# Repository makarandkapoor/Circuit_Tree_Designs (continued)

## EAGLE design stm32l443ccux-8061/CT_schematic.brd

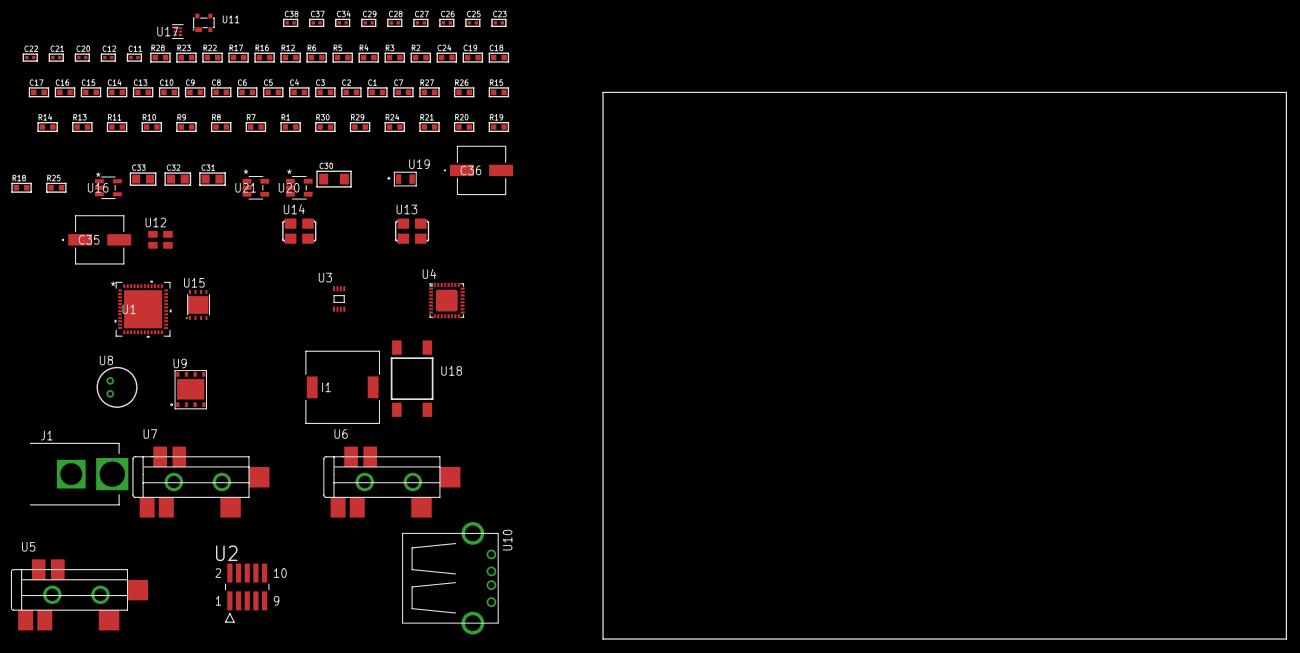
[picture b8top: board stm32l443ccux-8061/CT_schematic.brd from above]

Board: 2 copper layers, 100.0 x 80.0 mm, 91 parts (0 on the bottom side), 57 nets, no tracks yet.

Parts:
C1, C9, C13, C14, C15, C16, C17, C18, C19, C24: 1e-06; C0603
C2, C3, C4, C5, C6, C10: 1e-07; C0603
C7: 4.7e-06; C0603
C8: 1e-08; C0603
C11, C20, C21, C22, C23, C25, C34: 1e-07; C0402
C12, C26, C27, C28, C29, C37, C38: 1e-08; C0402
C30: 1e-05; C1206
C31, C32, C33: 1e-05; C0805
C35, C36: 0.0001; EXV-9H
I1: 5.2e-06; DR1040
J1: PJ-037B; PJ-037B_PACKAGE
R1, R7, R8, R9, R10, R11, R13, R14, R15, R26, R27: 10000.0; R0603
R2, R23: 1000.0; R0603
R3: 1600.5; R0603
R4: 4700.0; R0603
R5, R6: 2200.0; R0603
R12: 5.0; R0603
R16, R17: 1270.0; R0603
R18, R19, R20, R21: 100000.0; R0603
R22: 200.0; R0603
R24: 220000.0; R0603
R25: 1000000.0; R0603
R28: 9100.0; R0603
R29: 680000.0; R0603
R30: 120000.0; R0603
U1: STM32L443CCU6; UFQFPN48
U2: FTSH-105-01-L-DV-K; SAMTEC_FTSH-105-01-L-DV-K
U3: 24AA128T-I/MNY; TDFN-8/6MM
U4: SGTL5000XNAA3; QFN-32
U5, U6, U7: SJ-43515TS-SMT-TR
U8: WM-64PCT; WM-64PC
U9: SST26VF064B-104I/MF; WFDN-8
U10: 61400416021; USB-A-H
U11: prtr5v0u2ax; SOT143B
U12: ASEK-32.768KHz-ECST; ASEK
U13: ASFL-24.57MHZ-NCS; ASFL1
U14: ASFL1-25MHZ-NCS; ASFL1
U15: LP3878SDX-ADJ/NOPB; WSON-8
U16: ltc3406es5; TSOT-23-5
U17: TPS3895ADRYR; SON-6
U18: 4-1437565-2; SW_4-1437565-2
U19: Q65110A2395; LGM67K-G1J2-24-Z
U20, U21: nc7sz125m5x; NC7SZ125M5X

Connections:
CLK_U1_3: U1.3, U12.3
CLK_U1_5: U1.5, U14.3
CLK_U4_21: U4.21, U13.3
GND: C1.2, C2.2, C3.2, C4.2, C5.2, C6.2, C7.2, C8.2, C9.2, C10.2, C11.2, C12.2, C20.2, C21.2, C22.2, C23.2, C24.2, C25.2, C26.2, C27.2, C28.2, C29.2, C30.2, C31.2, C32.2, C33.1, C33.2, C34.2, C35.2, C36.2, C37.2, C38.2, J1.2, R2.2, R7.2, R11.2, R12.2, R14.2, R17.2, R23.2, R24.2, R28.2, R30.2, U1.8, U1.23, U1.35, U1.47, U1.49, U2.3, U2.5, U3.4, U3.7, U4.1, U4.3, U4.7, U4.EXP, U6.1, U7.1, U8.2, U9.4, U9.9, U10.4, U10.5, U10.6, U11.1, U12.2, U13.2, U14.2, U15.3, U15.PAD, U16.2, U17.2, U19.C, U20.2, U20.3, U21.1, U21.3
NET_U1_7: R4.1, U1.7, U21.4
NET_U1_30: R5.1, U1.30, U3.6
NET_U1_31: R6.1, U1.31, U3.5
NET_U1_44: R7.1, U1.44
NET_U1_45: R3.1, U1.45, U19.A
NET_U1_46: R1.1, U1.46, U18.3, U18.4
NET_U2_9: R12.1, U2.9
NET_U3_1: R13.1, U3.1
NET_U3_2: R14.1, U3.2
NET_U3_3: R15.1, U3.3
NET_U4_10: C23.1, U4.10
NET_U4_29: R16.1, U4.29
NET_U4_31: R17.1, U4.31
NET_U5_1: U4.4, U5.1
NET_U5_2: U4.2, U5.2
NET_U5_5: U4.6, U5.5
NET_U6_2: C14.1, U6.2
NET_U6_5: C13.1, U6.5
NET_U7_2: C16.1, C17.1, U7.2
NET_U7_5: C15.1, U7.5
NET_U7_13: C16.2, C17.2
NET_U8_1: C18.1, C19.1, C24.1, U4.16, U8.1
NET_U8_15: C18.2, C19.2
NET_U11_4: U10.1, U11.4
NET_U15_1: C29.1, U15.1
NET_U15_6: R22.2, R23.1, U15.6
NET_U15_8: R21.1, U15.8
NET_U16_3: I1.1, U16.3
NET_U16_5: R24.1, R25.1, U16.5
NET_U16_ATNET_3: I1.2, R25.2
NET_U17_1: R27.1, R28.1, U17.1
NET_U17_3: R29.2, R30.1, U17.3
NET_U17_4: R26.1, U17.4, U20.4, U21.2
NET_U18_1: R2.1, U18.1, U18.2
PROC_QUADSPI_BK1_IO0: U1.19, U9.5
PROC_QUADSPI_BK1_IO1: U1.18, U9.2
PROC_QUADSPI_BK1_IO2: R19.1, U1.17, U9.3
PROC_QUADSPI_BK1_IO3: R20.1, U1.16, U9.7
PROC_QUADSPI_BK1_NCS: R18.1, U1.12, U9.1
PROC_QUADSPI_CLK: U1.13, U9.6
PROC_SAI1_FS_A: U1.25, U4.23
PROC_SAI1_SCK_A: U1.21, U4.24
PROC_SAI1_SD_A: U1.28, U4.26
PROC_SYS_JTCK_SWCLK: R11.1, U1.37, U2.4
PROC_SYS_JTDI: R9.1, U1.38, U2.8
PROC_SYS_JTDO_SWO: U1.39, U2.6
PROC_SYS_JTMS_SWDIO: R10.1, U1.34, U2.2
PROC_USB_DM: U1.32, U10.2, U11.3
PROC_USB_DP: U1.33, U10.3, U11.2
RST_OUT_U2_JTAG_RST_B: R8.1, U2.10, U20.1
VCC_S1_4V8: C30.1, C32.1, C35.1, C36.1, J1.1, R21.2, U15.4, U16.4
VCC_TIER1_1V2: C20.1, C31.1, R22.1, U4.30, U15.5
VCC_TIER1_3V3: C1.1, C2.1, C3.1, C4.1, C5.1, C6.1, C7.1, C8.1, C9.1, C10.1, C11.1, C12.1, C21.1, C22.1, C25.1, C26.1, C27.1, C28.1, C33.2, C34.1, C37.1, C38.1, I1.2, R1.2, R3.2, R4.2, R5.2, R6.2, R8.2, R9.2, R10.2, R13.2, R15.2, R16.2, R18.2, R19.2, R20.2, R25.2, R26.2, R27.2, R29.1, U1.1, U1.9, U1.24, U1.36, U1.48, U2.1, U3.8, U4.5, U4.20, U9.8, U12.4, U13.4, U14.4, U17.6, U20.5, U21.5
